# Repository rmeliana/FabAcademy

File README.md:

# FabAcademy
Documentation of my project following Fab Academy instructions

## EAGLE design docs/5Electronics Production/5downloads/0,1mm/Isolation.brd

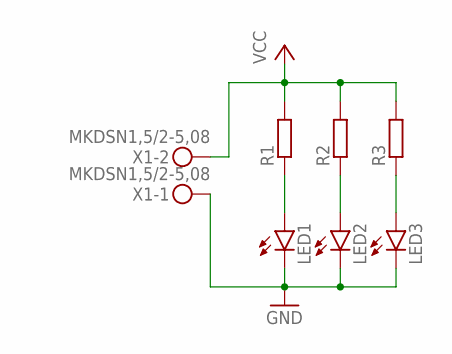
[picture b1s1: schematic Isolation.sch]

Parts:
LED1, LED2, LED3: LED5MM
R1, R2, R3: R-EU_0204/7; 0204/7
X1: MKDSN1,5/2-5,08

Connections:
GND: LED1.K (C), LED2.K (C), LED3.K (C), X1.1
unnamed: LED1.A, R1.1
unnamed: LED2.A, R2.1
unnamed: LED3.A, R3.1
VCC: R1.2, R2.2, R3.2, X1.2

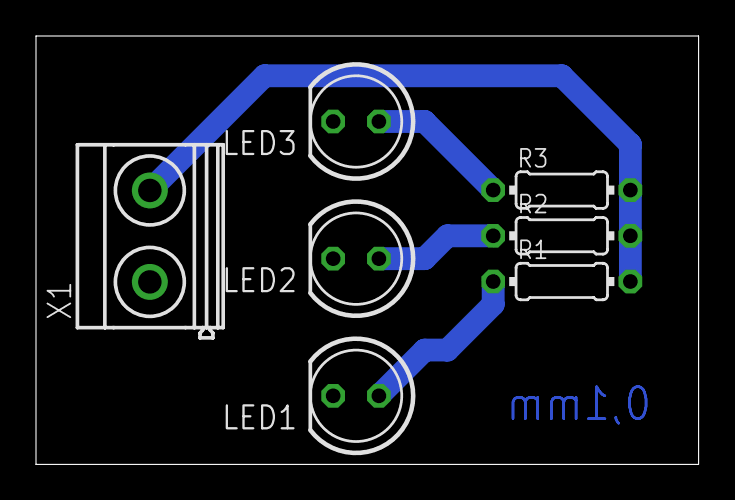
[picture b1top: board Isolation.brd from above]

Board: 2 copper layers, 36.8 x 23.8 mm, 7 parts (0 on the bottom side), 5 nets.

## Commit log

2021-06-08 transfer fileto GitHub
2021-06-08 upgraded About page
2021-06-08 added requirements.txt
2021-06-08 set up site_url
2021-06-08 test
2021-06-08 upgrade
2021-06-08 upgraded
2021-06-08 fix error plugin
2021-06-08 change size photo
2021-06-08 plugin git-revision-date
2021-06-10 git-revision-date plugin
2021-06-10 testing subtopics
2021-06-10 replace text
2021-06-10 last photos in about.md
2021-06-10 finished about.md
2021-06-10 congig pages
2021-06-10 assignments Principles and Practices
2021-06-10 fixed space between subject and link
2021-06-10 inspiring ideas
2021-06-10 Hexa video
2021-06-10 Hexa photo for video
2021-06-10 Hexa video test
2021-06-10 Hexa video test 2
2021-06-10 Hexa video test 3
2021-06-10 Hexa video test 4
2021-06-10 Hexa video test 5
2021-06-10 Hexa video test 6
2021-06-10 Hexa video test 7
2021-06-10 Hexa video test 8
2021-06-10 Hexa video test 9
2021-06-10 Hexa video test 10
2021-06-10 Hexa video test 11
2021-06-10 Hexa video test 12
2021-06-10 Hexa video test 13
2021-06-10 Hexa video test 14
2021-06-10 Hexa video adjusted size
2021-06-10 trying to organize the panel of video and photo
2021-06-10 fix subtopics label
2021-06-10 unhide label
2021-06-10 main topic
2021-06-11 center Hexa photo
2021-06-14 Hexa references
2021-06-14 center Hexa video
2021-06-14 Elowa explanation
2021-06-14 Hexa video size
2021-06-14 Hexa photo size
2021-06-14 Elowan photo
2021-06-14 organizing photo and video Elowan
2021-06-14 PNR starting
2021-06-14 PNR description
2021-06-15 finished description
2021-06-15 correction description
2021-06-15 Project Management page
2021-06-15 finished Principles and Practices page
2021-06-15 Assignment
2021-06-15 Adjusted pages titles
2021-06-17 Organizing pages
2021-06-17 completing Principles page
2021-06-17 Fab Academy Student Agreement
2021-06-17 resized photo
2021-06-17 resized photos
2021-06-18 add license
2021-06-25 changing the text About me
2021-06-25 create past for Principles and Practices
2021-06-25 path dor Principles and Practices folder
2021-06-25 correct files
2021-06-25 sketch sunlight sensor
2021-06-25 correct folder Principles
2021-06-25 photos
2021-06-25 sketch
2021-06-25 last sketches
2021-06-25 commercial sensor photo
2021-06-25 folders Project and CAD
2021-06-25 finished Principles and Practices
2021-06-25 starting Project Management
2021-06-25 introduction
2021-06-28 Correcting photos and text page
2021-06-28 Modified tips
2021-06-28 Git and GitHub
2021-06-30 changed name of site
2021-06-30 Steps
2021-06-30 adjusted folders
2021-06-30 GitBash terminal
2021-06-30 step 3
2021-06-30 aligned photo
2021-06-30 test alignment
2021-06-30 images alignment extension
2021-06-30 photo alignment
2021-06-30 left alignment
2021-06-30 center alignment
2021-06-30 center photo
2021-06-30 mkdocs material extension
2021-06-30 upgrade pip
2021-06-30 dependencies
2021-07-01 test of center an image
2021-07-01 finished center an image
2021-07-01 resize center image
2021-07-01 try to resize image
2021-07-01 historic of creating a site
2021-07-01 original form
2021-07-01 test numbers topic
2021-07-01 highlighter
2021-07-01 changed icons superfences
2021-07-01 corrected name of action file
2021-07-01 Part 1 Project Management
2021-07-01 emoji extensions
2021-07-02 added install mkdocs-material
2021-07-02 extension CSS for center images
2021-07-02 extra css
2021-07-06 image alignement
2021-07-06 extension tabbed
2021-07-06 Finished second assignment
2021-07-06 image alignment
2021-07-06 title About me
2021-07-06 new page
2021-07-07 corrected frame
2021-08-02 Finished translation
2021-08-03 address of action file
2021-08-06 CAD Assignment
2021-08-06 Starting
2021-08-10 Finishing Fusion part
2021-08-10 test 2
2021-08-11 almost finishing
2021-08-11 testing again
2021-08-11 Test without CAS Assignment
2021-08-11 correcting page CAD
2021-08-12 Finishing CAD Assignment
2021-08-12 Credit for my coworker and a student of Fab Academy
2021-08-17 corrected images
2021-08-17 Starting assignment 4
2021-08-18 Advice not advices
2021-08-20 Group assignment week CCC
2021-08-26 Vinyl cutter
2021-09-02 Vinyl and Parametric press-fit kit
2021-09-10 CCC assignment
2021-09-10 Electronics Production
2021-09-14 Finished CCC Assignment
2021-09-14 Isolation test
2021-10-05 Continuing Electronics Production
2021-10-05 test carousel
2021-10-05 test carousel programming
2021-11-30 last update
2021-11-30 Deployed ec68125 with MkDocs version: 1.2.3
